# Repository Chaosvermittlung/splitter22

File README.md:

# splitter22
Mini DSL/Analog Splitter

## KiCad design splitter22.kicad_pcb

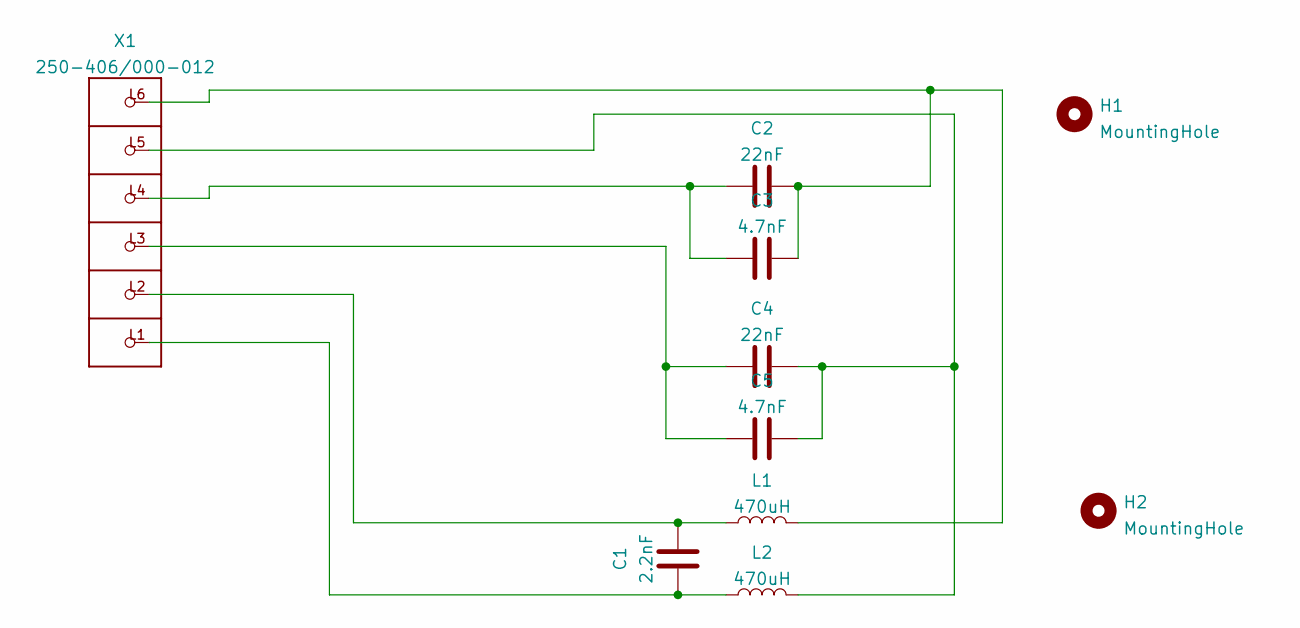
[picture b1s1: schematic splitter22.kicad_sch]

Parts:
C1: 2.2nF; C_Disc_D11.0mm_W5.0mm_P5.00mm
C2, C4: 22nF; C_Rect_L7.2mm_W8.5mm_P5.00mm_FKP2_FKP2_MKS2_MKP2
C3, C5: 4.7nF; C_Disc_D11.0mm_W5.0mm_P5.00mm
H1, H2: MountingHole; MountingHole_3.2mm_M3_DIN965_Pad_TopBottom
L1, L2: 470uH; L_Radial_D9.5mm_P5.00mm_Fastron_07HVP
X1: 250-406/000-012; P-250-406

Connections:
unnamed: C1.1, L2.1, X1.L1
unnamed: C1.2, L1.1, X1.L2
unnamed: C2.1, C3.1, X1.L4
unnamed: C2.2, C3.2, L1.2, X1.L6
unnamed: C4.1, C5.1, X1.L3
unnamed: C4.2, C5.2, L2.2, X1.L5

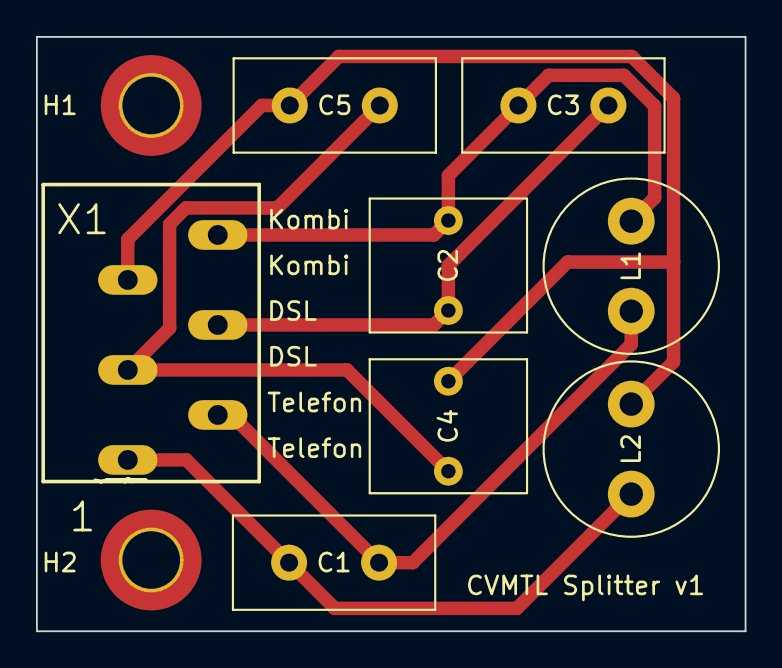
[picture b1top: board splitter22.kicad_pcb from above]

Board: 2 copper layers, 39.4 x 33.0 mm, 10 parts (0 on the bottom side), 6 nets.

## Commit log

2022-06-23 Add zips to ignore
2022-06-23 First Splitter Version
